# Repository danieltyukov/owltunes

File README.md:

<h1 align="center">OwlTunes</h1>

<p align="center"><b>Your music, one turn away.</b><br>
A Spotify remote with a round AMOLED face and a rotating ring. It charges on your desk and goes
with you in your pocket.</p>

<p align="center"><a href="https://danieltyukov.github.io/owltunes/">Website</a> |
<a href="docs/setup-guide.md">Setup guide</a> |
<a href="docs/design/2026-10-04-owltunes-system-design.md">System design</a> |
<a href="docs/hardware/README.md">Hardware</a></p>

OwlTunes controls the music that is already playing on your phone, laptop or speakers. Turn the
ring to change the volume, tap the cover to pause, press an ear to skip. Drop it on its perch and
it becomes a desk display that charges while it shows what is playing.

Spotify switched off every Car Thing in December 2024. Nobody can do that to OwlTunes: the
firmware, boards and enclosure are open source, it talks to Spotify's Web API directly over Wi-Fi,
and Bluetooth media keys keep working when there is no internet.

| On the desk | In your pocket |
|---|---|
|  |  |

## The device

| | |
|---|---|
| Display | 1.75 inch round AMOLED, 466 x 466, capacitive touch, behind 1.1 mm cover glass |
| Controls | Rotating ring with haptic detents, two ear buttons, a beak button, touch and swipe |
| Brain | ESP32-S3 with 16 MB flash and 8 MB PSRAM |
| Connectivity | Wi-Fi to the Spotify Web API (home network or phone hotspot); Bluetooth LE media keys offline |
| Sensors | Hall sensor for the ring, accelerometer (pick up to wake), ambient light |
| Power | Single-cell LiPo, USB-C, and spring-contact charging on the perch |
| Size | 66 x 84 x 24 mm |
| Perch | Weighted magnetic desk dock that holds the owl at 17.5 degrees |

## How you use it

| Control | Action |
|---|---|
| Ring | Volume on Now Playing; scroll in lists, one haptic tick per item |
| Tap the cover | Play or pause |
| Swipe left or right | Next or previous track |
| Left or right ear | Previous or next track |
| Hold the left ear, turn the ring | Pick one of 8 presets, release to play |
| Hold the right ear | Like the current track |
| Beak | Back; hold for Now Playing |

It also browses your playlists and library, searches, manages the queue and moves playback
between your Spotify Connect devices.

## What it looks like

The screens below come from the desktop simulator, which runs the same UI code as the firmware.

| Now playing | Playlists | Preset wheel | Looking for your phone |
|---|---|---|---|
|  |  |  |  |

## Inside

A 4-layer main board (KiCad 10, assembled by JLCPCB) inside a printed nylon enclosure (build123d,
MJF PA12). The ring carries magnets that a Hall sensor on the board reads, and a small linear
motor gives each detent its click. Every board passes ERC, DRC and a check against the enclosure's
mechanical contract in CI.

The renders on this page are made from the same files: the enclosure and board meshes go into
Blender with `tools/render.sh`, and the screen shows the simulator's output. The album art is a
generated placeholder. The renders were computed on the DelftBlue supercomputer of the Delft High
Performance Computing Centre (DHPC, https://www.tudelft.nl/dhpc), and the owl v0 renders on a TU
Delft EWI compute server.

## Owl v0

| Owl v0 | Inside owl v0 |
|---|---|
|  |  |

The first owl to be built is owl v0: the same face, ring, ears and beak, built round Waveshare's
ESP32-S3-Touch-AMOLED-1.75 kit, which brings the display, the ESP32-S3, USB-C and the battery
charger, so there is no board to order. Six nylon prints hold it, a Hall sensor module reads the
ring's magnets, and tact switches sit under the ears and the beak. It has no perch, haptics or light
sensor yet, and it is 19.7 mm deep. [kit-owl.md](docs/hardware/kit-owl.md) has the parts, wiring
and assembly.

## Status

- **Firmware:** Wi-Fi setup, Spotify linking and playback control run on an ESP32-S3 dev board
  against a real Spotify account, and are tested on the host and in QEMU. Display and touch
  drivers for the rev A board and the Waveshare AMOLED kit build in CI and wait for first light.
- **Owl v0:** the owl built round the Waveshare AMOLED kit, with the ring, ear and beak buttons
  and a 400 mAh cell, ready to order and print ([kit-owl.md](docs/hardware/kit-owl.md)).
- **Hardware rev A:** main board and perch board designed and checked; ordered after owl v0.
- **Enclosure v1:** owl, ring, bezel and perch ready for printing, with the face built around the
  panel's 52.6 mm cover glass.
- **Next:** owl v0 assembled and brought up, the button and ring drivers, then rev A.

Read the [system design](docs/design/2026-10-04-owltunes-system-design.md) for the full picture
and [docs/hardware](docs/hardware/README.md) for the boards.

## Set it up

OwlTunes needs Spotify Premium and your own free Spotify developer app (client ID). It uses the
Authorization Code flow with PKCE, so no client secret is stored on the device or in this
repository. Open the [setup page](https://danieltyukov.github.io/owltunes/setup/) in Chrome or
Edge, connect the owl over USB, add your Wi-Fi networks and client ID, and log in with Spotify.
The [setup guide](docs/setup-guide.md) walks through every step.

## Build it

<details>
<summary>Commands (Linux with CMake 3.22+, Ninja and a C compiler)</summary>

| What | Command |
|---|---|
| Unit tests (with sanitizers) | `tools/test_host.sh` |
| Simulator screenshot tests | `tools/sim.sh` |
| Interactive simulator (needs `libsdl2-dev`) | `cmake -S sim -B build/sim-sdl -G Ninja -DOWL_SIM_SDL=ON && cmake --build build/sim-sdl && build/sim-sdl/owl_sim sdl` |
| Firmware (ESP-IDF v6.1 activated) | `tools/firmware.sh build` |
| Firmware for the Arduino Nano ESP32, and flashing it | `tools/firmware.sh build nano_esp32`, then `tools/firmware.sh flash nano_esp32` |
| Firmware for the owl's rev A board or the Waveshare ESP32-S3-Touch-AMOLED-1.75 kit (display and touch; not yet run on hardware) | `tools/firmware.sh build owltunes_reva` or `tools/firmware.sh build waveshare_amoled_175`, then `flash` with the same board name |
| Hardware tests on the Nano ESP32 (board on USB) | `tools/hil_nano.py --wifi`; with a linked board and your consent, `tools/hil_spotify.py --real-account` |
| Firmware in the QEMU emulator | `tools/qemu_smoke.sh` |
| Setup protocol in QEMU, including a real HTTPS call to Spotify | `tools/qemu_prov_test.py` |
| Setup site: unit and browser tests (Node.js 22) | `cd web && npm ci && npm test && npm run e2e` |
| Setup site: local development server | `cd web && npm run dev` |
| Enclosure tests and exports | see [enclosure/README.md](enclosure/README.md) |
| Hardware checks (KiCad 10) | `tools/hw/check_all.sh` |
| Product renders (Blender 5.2, kicad-cli, uv) | `tools/render.sh` |
| Regenerate the UI fonts (needs Node.js) | `tools/gen_fonts.sh` |

</details>

| Path | Contents |
|---|---|
| `firmware/` | ESP-IDF firmware; shared C code in `firmware/components/`, board support in `firmware/boards/` |
| `sim/` | Desktop simulator and golden screenshots |
| `web/` | The setup site (TypeScript and Vite), published on GitHub Pages |
| `enclosure/` | build123d sources for the owl, owl v0 on the Waveshare kit, the ring and the perch |
| `hardware/` | KiCad 10 projects for the owl main board and the perch board |
| `docs/` | Design documents, hardware notes, setup and protocol guides |
| `tools/` | Build, test, style, render and font scripts |

The UI font is [Inter](https://rsms.me/inter/) (SIL Open Font License, see
`firmware/components/owl_ui/fonts/LICENSE-Inter.txt`).

## Licences

- Software: [MIT](LICENSE)
- Hardware and enclosure designs: [CERN-OHL-P-2.0](LICENSE-HARDWARE)

## Not affiliated with Spotify

OwlTunes is an independent, non-commercial project. It is not affiliated with, endorsed by or
sponsored by Spotify. Spotify is a trademark of Spotify AB.

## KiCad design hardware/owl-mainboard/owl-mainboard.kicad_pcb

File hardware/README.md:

# OwlTunes hardware

KiCad 10 projects for the owl main board (`owl-mainboard/`, 4 layers) and the perch board with its
snap-off owl dock-pad section (`perch-dock/`, 2 layers). Shared symbols and footprints are in
`lib/`. Licence: CERN-OHL-P-2.0 (`LICENSE-HARDWARE`).

Documentation: docs/hardware/README.md.

Each board has a `design.toml` that lists every part, its LCSC number and its pin-to-net map. The
schematic must match it exactly:

| Command | Checks |
|---|---|
| `tools/hw/check_all.sh` | Everything below, as CI runs it |
| `python3 tools/hw/hw_titleblock.py --check owl-mainboard` | Title blocks (title, Rev A, company, licence, date) of every schematic and the PCB; without `--check` it writes them |
| `python3 tools/hw/hw_netlist.py owl-mainboard` | Connectivity against `design.toml` |
| `python3 tools/hw/hw_bom.py owl-mainboard` | `LCSC Part #` and `MPN` fields |
| `python3 tools/hw/hw_kicad.py` | ERC (and DRC once enabled in `boards.toml`), reports in `build/hardware/` |
| `python3 tools/hw/hw_contract.py check owl-mainboard` | Outline and fixed parts against the enclosure contract |
| `python3 tools/hw/hw_stock.py owl-mainboard --boards 5` | JLCPCB stock (needs network) |

`tools/hw/hw_setup.py <board>` applies `setup.toml` (stackup, origins, JLCPCB rules, net classes).
The stackup in `setup.toml` is written into each PCB by `hw_setup.py`. Main board: JLCPCB 4-layer
1.0 mm, modelled on JLC04101H-7628 (35 um outer copper, 7628 prepreg 0.2104 mm, 15.2 um inner
copper); the core thickness (0.4788 mm) is chosen so the stack adds up to 1.0 mm and is to be
confirmed against https://jlcpcb.com/impedance on the order day. Perch board: 2-layer 1.6 mm FR-4.
A test checks that each stack adds up to the board thickness.

`hw_stock.py` writes prices only below the main checkout's `private/` folder.

Coordinates: the display centre is at (100, 100) on the board page, with X right and Y down.
Fabrication outputs (`production/`) are generated, not tracked; releases carry them.

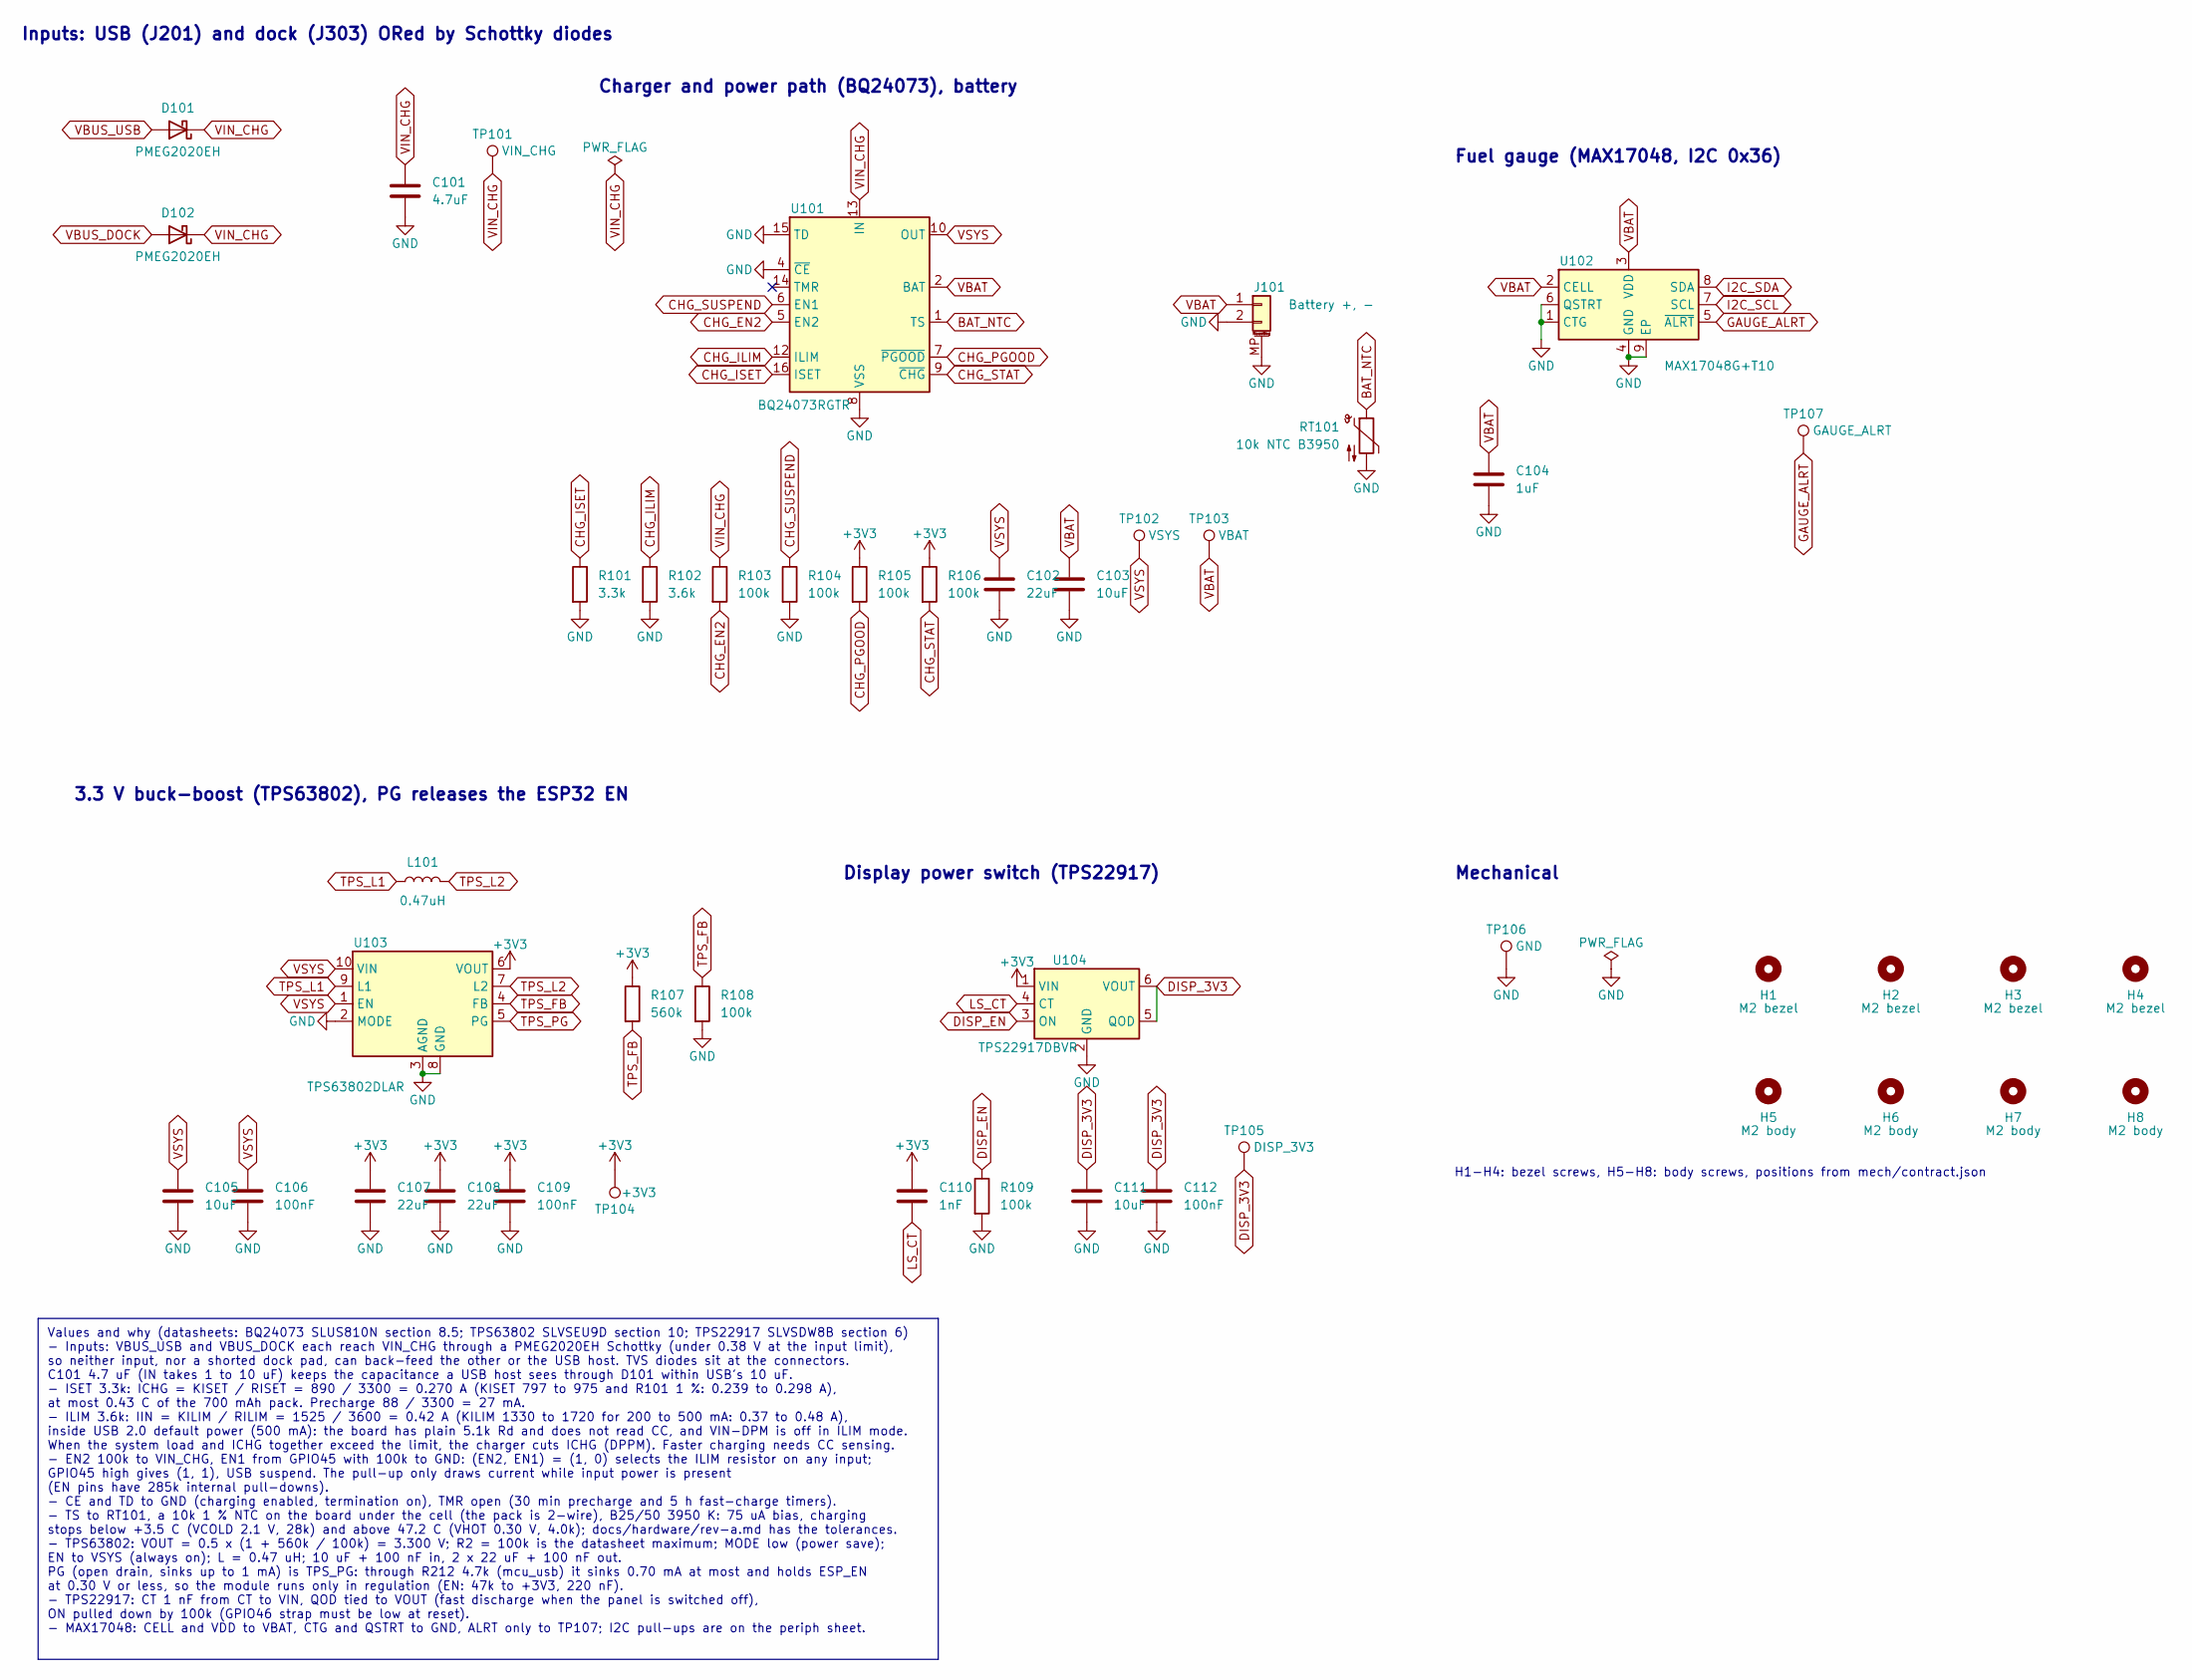
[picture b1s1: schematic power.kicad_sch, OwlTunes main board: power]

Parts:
C101: 4.7uF; C_0603_1608Metric; MPN CL10A475KO8NNNC; LCSC Part # C19666
C102, C107, C108: 22uF; C_0603_1608Metric; MPN CL10A226MQ8NRNC; LCSC Part # C59461
C103, C105, C111: 10uF; C_0603_1608Metric; MPN CL10A106KP8NNNC; LCSC Part # C19702
C104: 1uF; C_0402_1005Metric; MPN CL05A105KA5NQNC; LCSC Part # C52923
C106, C109, C112: 100nF; C_0402_1005Metric; MPN CL05B104KO5NNNC; LCSC Part # C1525
C110: 1nF; C_0402_1005Metric; MPN 0402B102K500NT; LCSC Part # C1523
D101, D102: PMEG2020EH; D_SOD-123F; MPN PMEG2020EH,115; LCSC Part # C456104
H1, H2, H3, H4: M2 bezel; MountingHole_2.2mm_M2
H5, H6, H7, H8: M2 body; MountingHole_2.2mm_M2
J101: Battery +, -; JST_PH_S2B-PH-SM4-TB_1x02-1MP_P2.00mm_Horizontal; MPN S2B-PH-SM4-TB(LF)(SN); LCSC Part # C295747
L101: 0.47uH; L_Murata_DFE201612E; MPN DFE201612E-R47M=P2; LCSC Part # C668312
R101: 3.3k; R_0402_1005Metric; MPN 0402WGF3301TCE; LCSC Part # C25890
R102: 3.6k; R_0402_1005Metric; MPN 0402WGF3601TCE; LCSC Part # C25891
R103, R104, R105, R106, R108, R109: 100k; R_0402_1005Metric; MPN 0402WGF1003TCE; LCSC Part # C25741
R107: 560k; R_0402_1005Metric; MPN 0402WGF5603TCE; LCSC Part # C132339
RT101: 10k NTC B3950; R_0402_1005Metric; MPN SDNT1005X103F3950FTF; LCSC Part # C95939
TP101: VIN_CHG; TestPoint_Pad_D1.0mm
TP102: VSYS; TestPoint_Pad_D1.0mm
TP103: VBAT; TestPoint_Pad_D1.0mm
TP104: +3V3; TestPoint_Pad_D1.0mm
TP105: DISP_3V3; TestPoint_Pad_D1.0mm
TP106: GND; TestPoint_Pad_D1.0mm
TP107: GAUGE_ALRT; TestPoint_Pad_D1.0mm
U101: BQ24073RGTR; VQFN-16-1EP_3x3mm_P0.5mm_EP1.6x1.6mm_ThermalVias_Drill0.3; MPN BQ24073RGTR; LCSC Part # C15220
U102: MAX17048G+T10; Maxim_TDFN-8-1EP_2x2mm_P0.5mm; MPN MAX17048G+T10; LCSC Part # C2682616
U103: TPS63802DLAR; TI_DLA_VSON-10_2x3mm_P0.5mm; MPN TPS63802DLAR; LCSC Part # C2845237
U104: TPS22917DBVR; SOT-23-6; MPN TPS22917DBVR; LCSC Part # C2681320

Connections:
+3V3: C107.1, C108.1, C109.1, C110.1, R105.1, R106.1, R107.1, TP104.1, U103.6 (VOUT), U104.1 (VIN); also elsewhere on the board
BAT_NTC: RT101.1, U101.1 (TS)
CHG_EN2: R103.2, U101.5 (EN2)
CHG_ILIM: R102.1, U101.12 (ILIM)
CHG_ISET: R101.1, U101.16 (ISET)
CHG_PGOOD: R105.2, U101.7 (~PGOOD); also elsewhere on the board
CHG_STAT: R106.2, U101.9 (~CHG); also elsewhere on the board
CHG_SUSPEND: R104.1, U101.6 (EN1); also elsewhere on the board
DISP_3V3: C111.1, C112.1, TP105.1, U104.5 (QOD), U104.6 (VOUT); also elsewhere on the board
DISP_EN: R109.1, U104.3 (ON); also elsewhere on the board
GAUGE_ALRT: TP107.1, U102.5 (~ALRT)
GND: C101.2, C102.2, C103.2, C104.2, C105.2, C106.2, C107.2, C108.2, C109.2, C111.2, C112.2, J101.2, J101.MP (MountPin), R101.2, R102.2, R104.2, R108.2, R109.2, RT101.2, TP106.1, U101.4 (~CE), U101.8 (VSS), U101.15 (TD), U101.17 (VSS), U102.1 (CTG), U102.4 (GND), U102.6 (QSTRT), U102.9 (EP), U103.2 (MODE), U103.3 (AGND), U103.8 (GND), U104.2 (GND); also elsewhere on the board
I2C_SCL: U102.7 (SCL); also elsewhere on the board
I2C_SDA: U102.8 (SDA); also elsewhere on the board
LS_CT: C110.2, U104.4 (CT)
TPS_FB: R107.2, R108.1, U103.4 (FB)
TPS_L1: L101.1, U103.9 (L1)
TPS_L2: L101.2, U103.7 (L2)
TPS_PG: U103.5 (PG); also elsewhere on the board
VBAT: C103.1, C104.1, J101.1, TP103.1, U101.2 (BAT), U101.3 (BAT), U102.2 (CELL), U102.3 (VDD)
VBUS_DOCK: D102.2 (A); also elsewhere on the board
VBUS_USB: D101.2 (A); also elsewhere on the board
VIN_CHG: C101.1, D101.1 (K), D102.1 (K), R103.1, TP101.1, U101.13 (IN)
VSYS: C102.1, C105.1, C106.1, TP102.1, U101.10 (OUT), U101.11 (OUT), U103.1 (EN), U103.10 (VIN)

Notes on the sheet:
Charger and power path (BQ24073), battery
3.3 V buck-boost (TPS63802), PG releases the ESP32 EN
Fuel gauge (MAX17048, I2C 0x36)
Display power switch (TPS22917)
Mechanical
H1-H4: bezel screws, H5-H8: body screws, positions from mech/contract.json
Inputs: USB (J201) and dock (J303) ORed by Schottky diodes
Values and why (datasheets: BQ24073 SLUS810N section 8.5; TPS63802 SLVSEU9D section 10; TPS22917 SLVSDW8B section 6) - Inputs: VBUS_USB and VBUS_DOCK each reach VIN_CHG through a PMEG2020EH Schottky (under 0.38 V at the input limit), so neither input, nor a shorted dock pad, can back-feed the other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

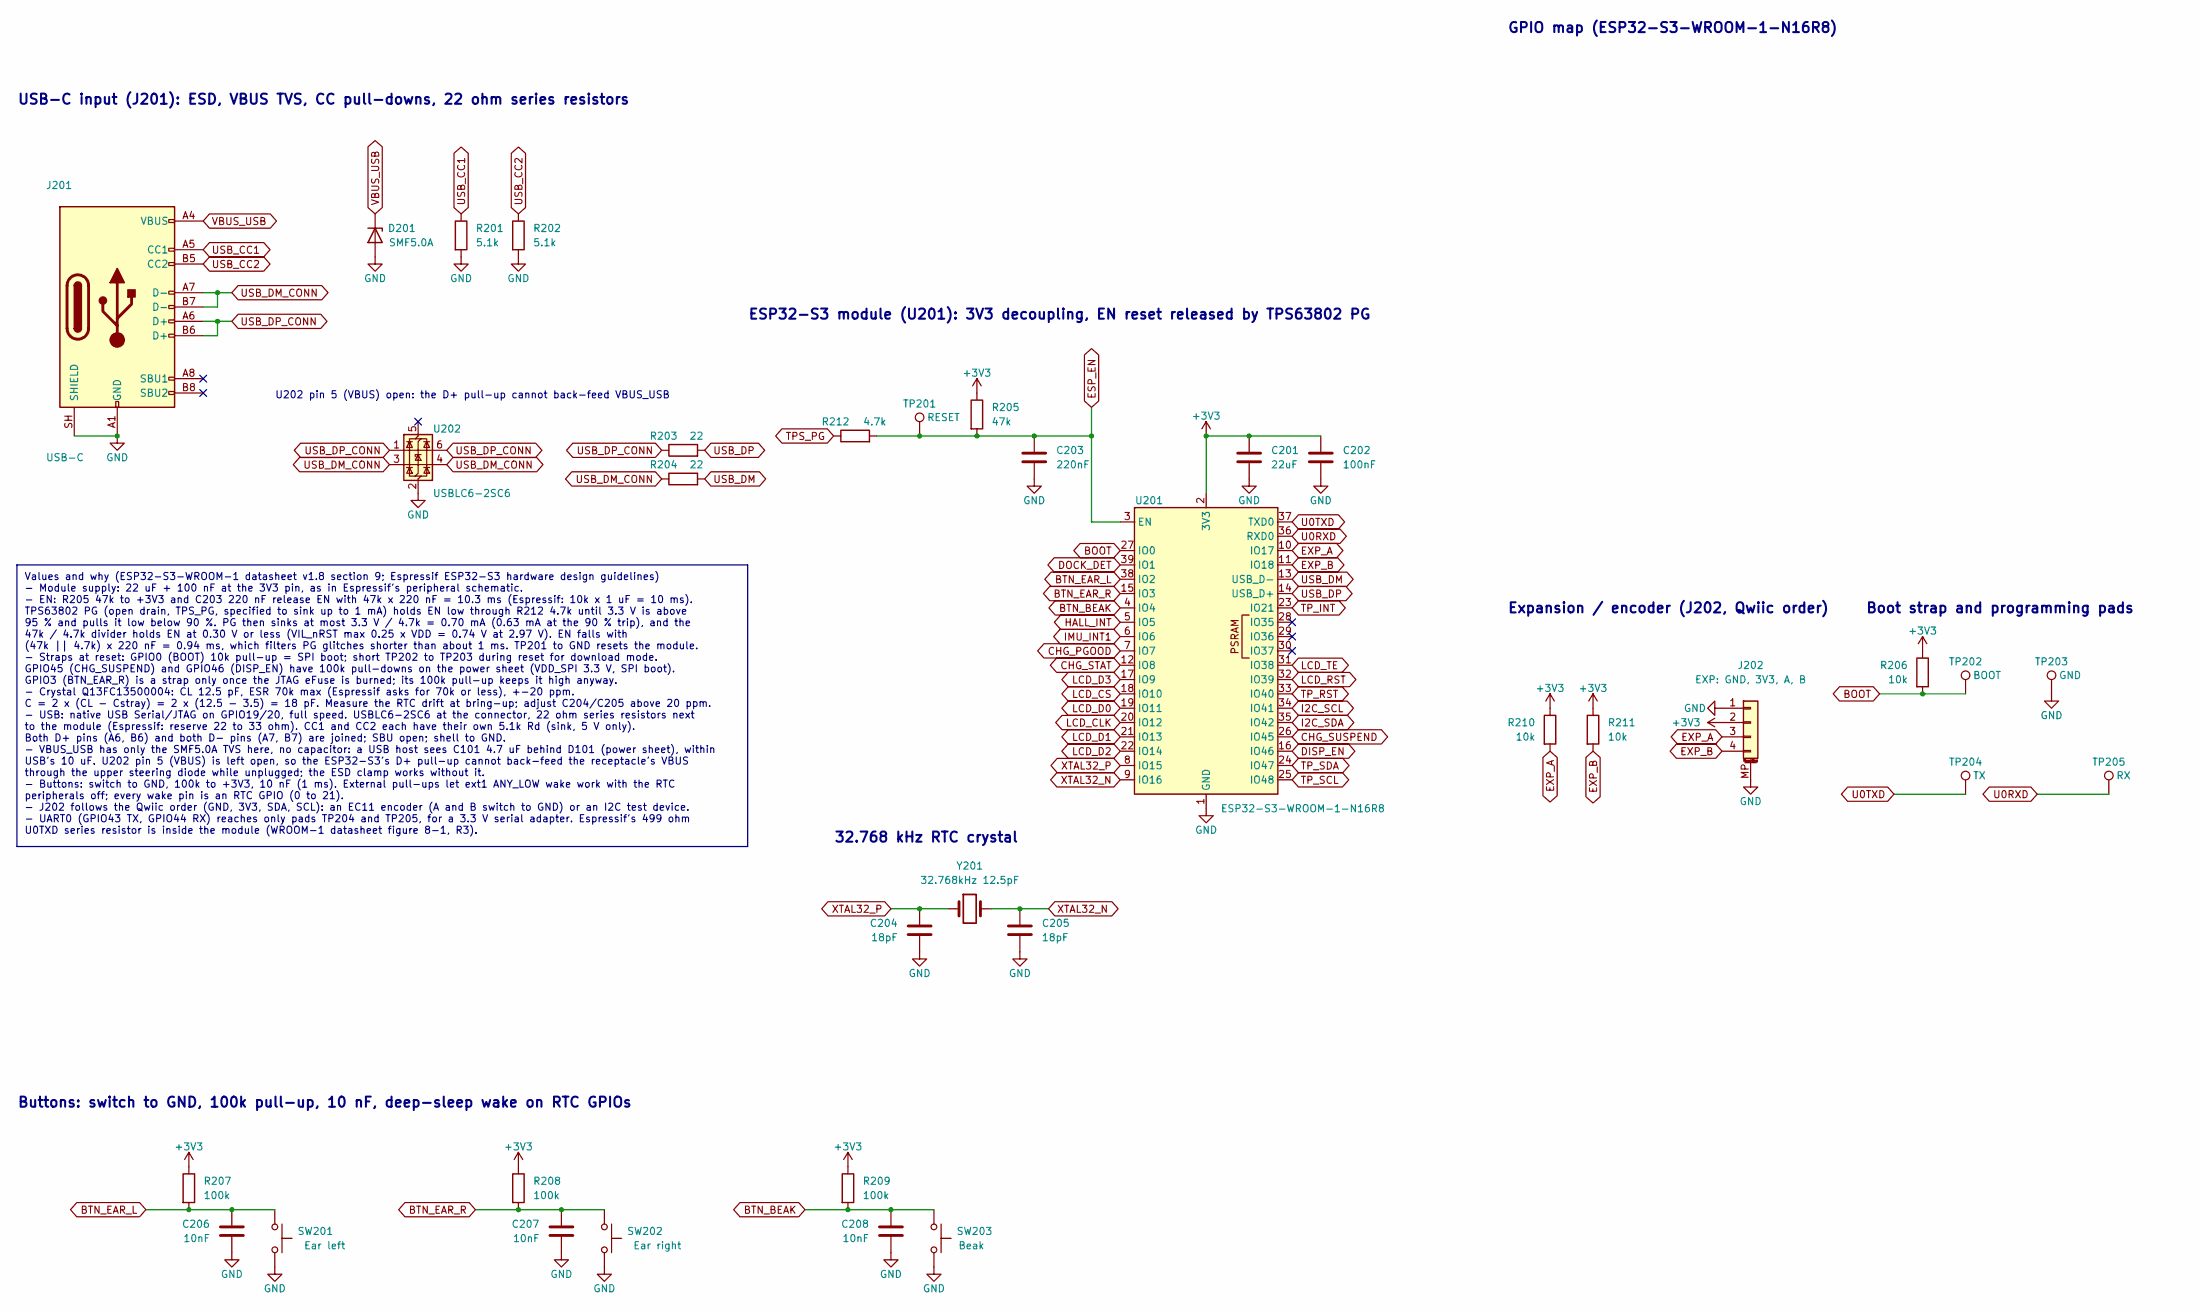
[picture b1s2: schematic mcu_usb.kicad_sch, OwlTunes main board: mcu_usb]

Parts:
C201: 22uF; C_0603_1608Metric; MPN CL10A226MQ8NRNC; LCSC Part # C59461
C202: 100nF; C_0402_1005Metric; MPN CL05B104KO5NNNC; LCSC Part # C1525
C203: 220nF; C_0402_1005Metric; MPN CL05B224KO5NNNC; LCSC Part # C16772
C204, C205: 18pF; C_0402_1005Metric; MPN 0402CG180J500NT; LCSC Part # C1549
C206, C207, C208: 10nF; C_0402_1005Metric; MPN CL05B103KB5NNNC; LCSC Part # C15195
D201: SMF5.0A; D_SOD-123F; MPN SMF5.0A; LCSC Part # C193402
J201: USB-C; USB_C_Receptacle_HRO_TYPE-C-31-M-12; MPN TYPE-C-31-M-12; LCSC Part # C165948
J202: EXP: GND, 3V3, A, B; JST_SH_SM04B-SRSS-TB_1x04-1MP_P1.00mm_Horizontal; MPN SM04B-SRSS-TB(LF)(SN); LCSC Part # C160404
R201, R202: 5.1k; R_0402_1005Metric; MPN 0402WGF5101TCE; LCSC Part # C25905
R203, R204: 22; R_0402_1005Metric; MPN 0402WGF220JTCE; LCSC Part # C25092
R205: 47k; R_0402_1005Metric; MPN 0402WGF4702TCE; LCSC Part # C25792
R206, R210, R211: 10k; R_0402_1005Metric; MPN 0402WGF1002TCE; LCSC Part # C25744
R207, R208, R209: 100k; R_0402_1005Metric; MPN 0402WGF1003TCE; LCSC Part # C25741
R212: 4.7k; R_0402_1005Metric; MPN 0402WGF4701TCE; LCSC Part # C25900
SW201: Ear left; SW_SPST_EVQP7A; MPN EVQP7A01P; LCSC Part # C79167
SW202: Ear right; SW_SPST_EVQP7A; MPN EVQP7A01P; LCSC Part # C79167
SW203: Beak; SW_SPST_TS-1088-xR020; MPN TS-1088-AR02016; LCSC Part # C720477
TP201: RESET; TestPoint_Pad_D1.5mm
TP202: BOOT; TestPoint_Pad_D1.5mm
TP203: GND; TestPoint_Pad_D1.5mm
TP204: TX; TestPoint_Pad_D1.0mm
TP205: RX; TestPoint_Pad_D1.0mm
U201: ESP32-S3-WROOM-1-N16R8; ESP32-S3-WROOM-1_Drill0.3; MPN ESP32-S3-WROOM-1-N16R8; LCSC Part # C2913202
U202: USBLC6-2SC6; SOT-23-6; MPN USBLC6-2SC6; LCSC Part # C7519
Y201: 32.768kHz 12.5pF; Crystal_SMD_3215-2Pin_3.2x1.5mm; MPN Q13FC13500004; LCSC Part # C32346

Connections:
+3V3: C201.1, C202.1, J202.2, R205.1, R206.1, R207.1, R208.1, R209.1, R210.1, R211.1, U201.2 (3V3); also elsewhere on the board
BOOT: R206.2, TP202.1, U201.27 (IO0)
BTN_BEAK: C208.1, R209.2, SW203.1, U201.4 (IO4)
BTN_EAR_L: C206.1, R207.2, SW201.1, U201.38 (IO2)
BTN_EAR_R: C207.1, R208.2, SW202.1, U201.15 (IO3)
CHG_PGOOD: U201.7 (IO7); also elsewhere on the board
CHG_STAT: U201.12 (IO8); also elsewhere on the board
CHG_SUSPEND: U201.26 (IO45); also elsewhere on the board
DISP_EN: U201.16 (IO46); also elsewhere on the board
DOCK_DET: U201.39 (IO1); also elsewhere on the board
ESP_EN: C203.1, R205.2, R212.2, TP201.1, U201.3 (EN)
EXP_A: J202.3, R210.2, U201.10 (IO17)
EXP_B: J202.4, R211.2, U201.11 (IO18)
GND: C201.2, C202.2, C203.2, C204.2, C205.2, C206.2, C207.2, C208.2, D201.2 (A), J201.A1 (GND), J201.A12 (GND), J201.B1 (GND), J201.B12 (GND), J201.SH (SHIELD), J202.1, J202.MP (MountPin), R201.2, R202.2, SW201.2, SW202.2, SW203.2, TP203.1, U201.1 (GND), U201.40 (GND), U201.41 (GND), U202.2 (GND); also elsewhere on the board
HALL_INT: U201.5 (IO5); also elsewhere on the board
I2C_SCL: U201.34 (IO41); also elsewhere on the board
I2C_SDA: U201.35 (IO42); also elsewhere on the board
IMU_INT1: U201.6 (IO6); also elsewhere on the board
LCD_CLK: U201.20 (IO12); also elsewhere on the board
LCD_CS: U201.18 (IO10); also elsewhere on the board
LCD_D0: U201.19 (IO11); also elsewhere on the board
LCD_D1: U201.21 (IO13); also elsewhere on the board
LCD_D2: U201.22 (IO14); also elsewhere on the board
LCD_D3: U201.17 (IO9); also elsewhere on the board
LCD_RST: U201.32 (IO39); also elsewhere on the board
LCD_TE: U201.31 (IO38); also elsewhere on the board
TPS_PG: R212.1; also elsewhere on the board
TP_INT: U201.23 (IO21); also elsewhere on the board
TP_RST: U201.33 (IO40); also elsewhere on the board
TP_SCL: U201.25 (IO48); also elsewhere on the board
TP_SDA: U201.24 (IO47); also elsewhere on the board
U0RXD: TP205.1, U201.36 (RXD0)
U0TXD: TP204.1, U201.37 (TXD0)
USB_CC1: J201.A5 (CC1), R201.1
USB_CC2: J201.B5 (CC2), R202.1
USB_DM: R204.2, U201.13 (USB_D-)
USB_DM_CONN: J201.A7 (D-), J201.B7 (D-), R204.1, U202.3 (I/O2), U202.4 (I/O2)
USB_DP: R203.2, U201.14 (USB_D+)
USB_DP_CONN: J201.A6 (D+), J201.B6 (D+), R203.1, U202.1 (I/O1), U202.6 (I/O1)
VBUS_USB: D201.1 (K), J201.A4 (VBUS), J201.A9 (VBUS), J201.B4 (VBUS), J201.B9 (VBUS); also elsewhere on the board
XTAL32_N: C205.1, U201.9 (IO16), Y201.2
XTAL32_P: C204.1, U201.8 (IO15), Y201.1

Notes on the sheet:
GPIO map (ESP32-S3-WROOM-1-N16R8)
USB-C input (J201): ESD, VBUS TVS, CC pull-downs, 22 ohm series resistors
ESP32-S3 module (U201): 3V3 decoupling, EN reset released by TPS63802 PG
Boot strap and programming pads
Buttons: switch to GND, 100k pull-up, 10 nF, deep-sleep wake on RTC GPIOs
U202 pin 5 (VBUS) open: the D+ pull-up cannot back-feed VBUS_USB
Expansion / encoder (J202, Qwiic order)
32.768 kHz RTC crystal
Values and why (ESP32-S3-WROOM-1 datasheet v1.8 section 9; Espressif ESP32-S3 hardware design guidelines) - Module supply: 22 uF + 100 nF at the 3V3 pin, as in Espressif's peripheral schematic. - EN: R205 47k to +3V3 and C203 220 nF release EN with 47k x 220 nF = 10.3 ms (Espressif: 10k x 1 uF = 10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

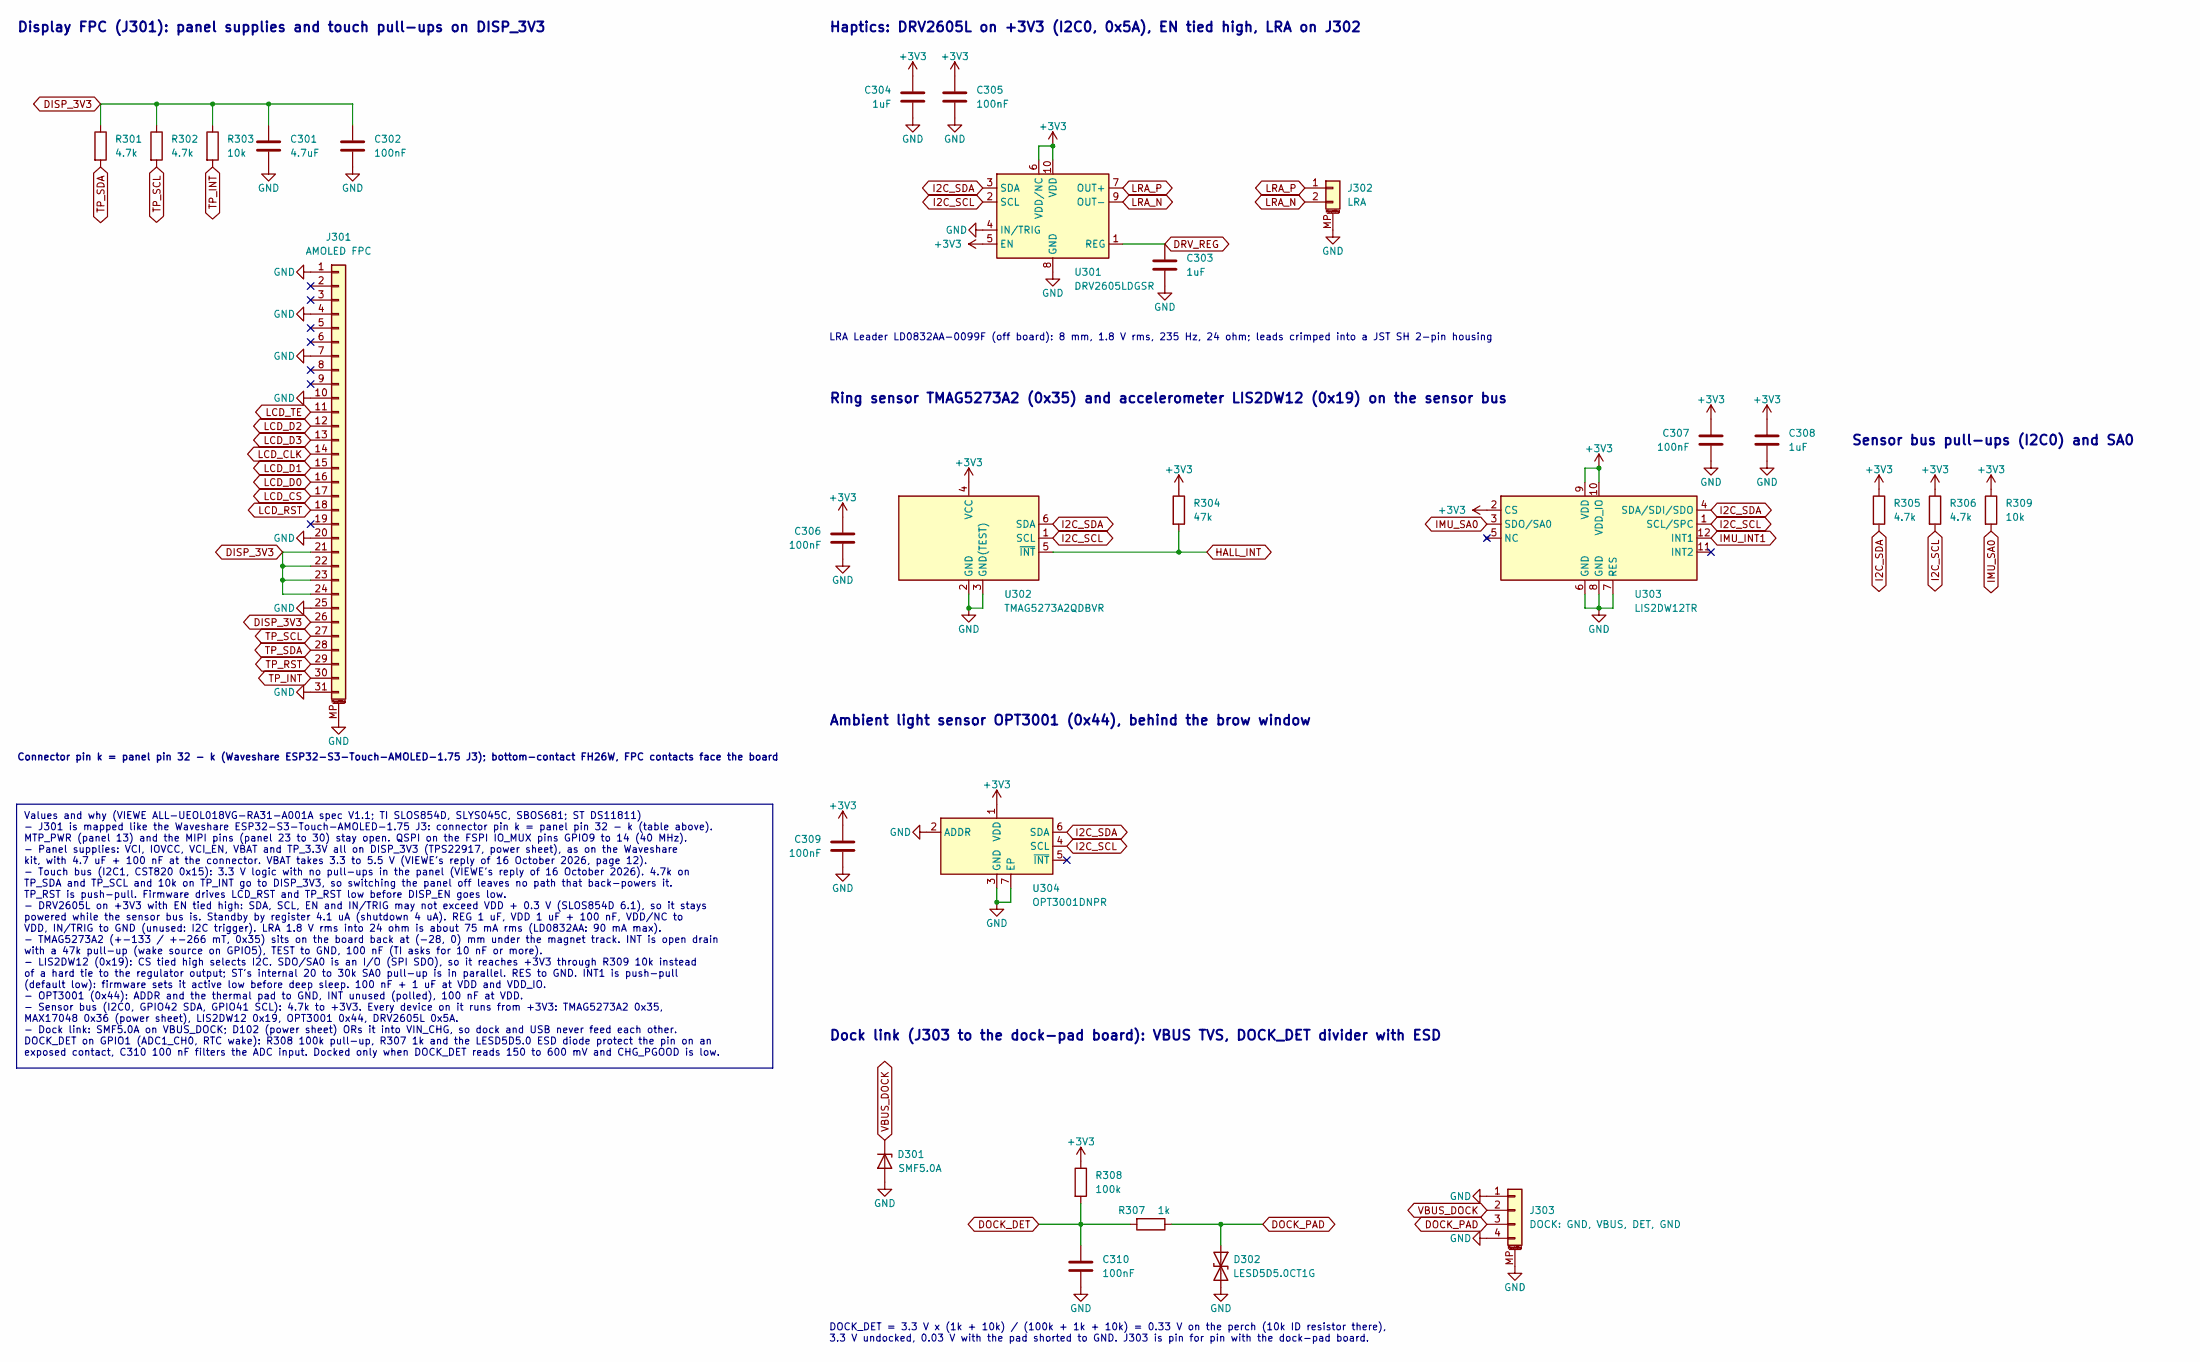
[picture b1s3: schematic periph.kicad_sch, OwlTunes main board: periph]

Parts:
C301: 4.7uF; C_0402_1005Metric; MPN CL05A475MP5NRNC; LCSC Part # C23733
C302, C305, C306, C307, C309, C310: 100nF; C_0402_1005Metric; MPN CL05B104KO5NNNC; LCSC Part # C1525
C303, C304, C308: 1uF; C_0402_1005Metric; MPN CL05A105KA5NQNC; LCSC Part # C52923
D301: SMF5.0A; D_SOD-123F; MPN SMF5.0A; LCSC Part # C193402
D302: LESD5D5.0CT1G; D_SOD-523; MPN LESD5D5.0CT1G; LCSC Part # C5274290
J301: AMOLED FPC; Hirose_FH26W-31S-0.3SHW_1x31-1MP_P0.30mm_Horizontal; MPN FH26W-31S-0.3SHW(60); LCSC Part # C2973806
J302: LRA; JST_SH_SM02B-SRSS-TB_1x02-1MP_P1.00mm_Horizontal; MPN SM02B-SRSS-TB(LF)(SN); LCSC Part # C160402
J303: DOCK: GND, VBUS, DET, GND; JST_SH_SM04B-SRSS-TB_1x04-1MP_P1.00mm_Horizontal; MPN SM04B-SRSS-TB(LF)(SN); LCSC Part # C160404
R301, R302, R305, R306: 4.7k; R_0402_1005Metric; MPN 0402WGF4701TCE; LCSC Part # C25900
R303, R309: 10k; R_0402_1005Metric; MPN 0402WGF1002TCE; LCSC Part # C25744
R304: 47k; R_0402_1005Metric; MPN 0402WGF4702TCE; LCSC Part # C25792
R307: 1k; R_0402_1005Metric; MPN 0402WGF1001TCE; LCSC Part # C11702
R308: 100k; R_0402_1005Metric; MPN 0402WGF1003TCE; LCSC Part # C25741
U301: DRV2605LDGSR; TSSOP-10_3x3mm_P0.5mm; MPN DRV2605LDGSR; LCSC Part # C527464
U302: TMAG5273A2QDBVR; SOT-23-6; MPN TMAG5273A2QDBVR; LCSC Part # C3715882
U303: LIS2DW12TR; LGA-12_2x2mm_P0.5mm; MPN LIS2DW12TR; LCSC Part # C189624
U304: OPT3001DNPR; TI_DNP_USON-6-1EP_2x2mm_P0.65mm; MPN OPT3001DNPR; LCSC Part # C90462

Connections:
+3V3: C304.1, C305.1, C306.1, C307.1, C308.1, C309.1, R304.1, R305.1, R306.1, R308.1, R309.1, U301.5 (EN), U301.6 (VDD/NC), U301.10 (VDD), U302.4 (VCC), U303.2 (CS), U303.9 (VDD), U303.10 (VDD_IO), U304.1 (VDD); also elsewhere on the board
DISP_3V3: C301.1, C302.1, J301.21, J301.22, J301.23, J301.24, J301.26, R301.1, R302.1, R303.1; also elsewhere on the board
DOCK_DET: C310.1, R307.2, R308.2; also elsewhere on the board
DOCK_PAD: D302.1 (A1), J303.3, R307.1
DRV_REG: C303.1, U301.1 (REG)
GND: C301.2, C302.2, C303.2, C304.2, C305.2, C306.2, C307.2, C308.2, C309.2, C310.2, D301.2 (A), D302.2 (A2), J301.1, J301.4, J301.7, J301.10, J301.20, J301.25, J301.31, J301.MP (MountPin), J302.MP (MountPin), J303.1, J303.4, J303.MP (MountPin), U301.4 (IN/TRIG), U301.8 (GND), U302.2 (GND), U302.3 (GND(TEST)), U303.6 (GND), U303.7 (RES), U303.8 (GND), U304.2 (ADDR), U304.3 (GND), U304.7 (EP); also elsewhere on the board
HALL_INT: R304.2, U302.5 (~INT); also elsewhere on the board
I2C_SCL: R306.2, U301.2 (SCL), U302.1 (SCL), U303.1 (SCL/SPC), U304.4 (SCL); also elsewhere on the board
I2C_SDA: R305.2, U301.3 (SDA), U302.6 (SDA), U303.4 (SDA/SDI/SDO), U304.6 (SDA); also elsewhere on the board
IMU_INT1: U303.12 (INT1); also elsewhere on the board
IMU_SA0: R309.2, U303.3 (SDO/SA0)
LCD_CLK: J301.14; also elsewhere on the board
LCD_CS: J301.17; also elsewhere on the board
LCD_D0: J301.16; also elsewhere on the board
LCD_D1: J301.15; also elsewhere on the board
LCD_D2: J301.12; also elsewhere on the board
LCD_D3: J301.13; also elsewhere on the board
LCD_RST: J301.18; also elsewhere on the board
LCD_TE: J301.11; also elsewhere on the board
LRA_N: J302.2, U301.9 (OUT-)
LRA_P: J302.1, U301.7 (OUT+)
TP_INT: J301.30, R303.2; also elsewhere on the board
TP_RST: J301.29; also elsewhere on the board
TP_SCL: J301.27, R302.2; also elsewhere on the board
TP_SDA: J301.28, R301.2; also elsewhere on the board
VBUS_DOCK: D301.1 (K), J303.2; also elsewhere on the board

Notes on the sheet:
LRA Leader LD0832AA-0099F (off board): 8 mm, 1.8 V rms, 235 Hz, 24 ohm; leads crimped into a JST SH 2-pin housing
Sensor bus pull-ups (I2C0) and SA0
Ambient light sensor OPT3001 (0x44), behind the brow window
Dock link (J303 to the dock-pad board): VBUS TVS, DOCK_DET divider with ESD
Haptics: DRV2605L on +3V3 (I2C0, 0x5A), EN tied high, LRA on J302
Display FPC (J301): panel supplies and touch pull-ups on DISP_3V3
Connector pin k = panel pin 32 - k (Waveshare ESP32-S3-Touch-AMOLED-1.75 J3); bottom-contact FH26W, FPC contacts face the board
Ring sensor TMAG5273A2 (0x35) and accelerometer LIS2DW12 (0x19) on the sensor bus
DOCK_DET = 3.3 V x (1k + 10k) / (100k + 1k + 10k) = 0.33 V on the perch (10k ID resistor there), 3.3 V undocked, 0.03 V with the pad shorted to GND. J303 is pin for pin with the dock-pad board.
Values and why (VIEWE ALL-UEOL018VG-RA31-A001A spec V1.1; TI SLOS854D, SLYS045C, SBOS681; ST DS11811) - J301 is mapped like the Waveshare ESP32-S3-Touch-AMOLED-1.75 J3: connector pin k = panel pin 32 - k (table above). MTP_PWR (panel 13) and the MIPI pins (panel 23 to 30) stay open. QSPI on the FSP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

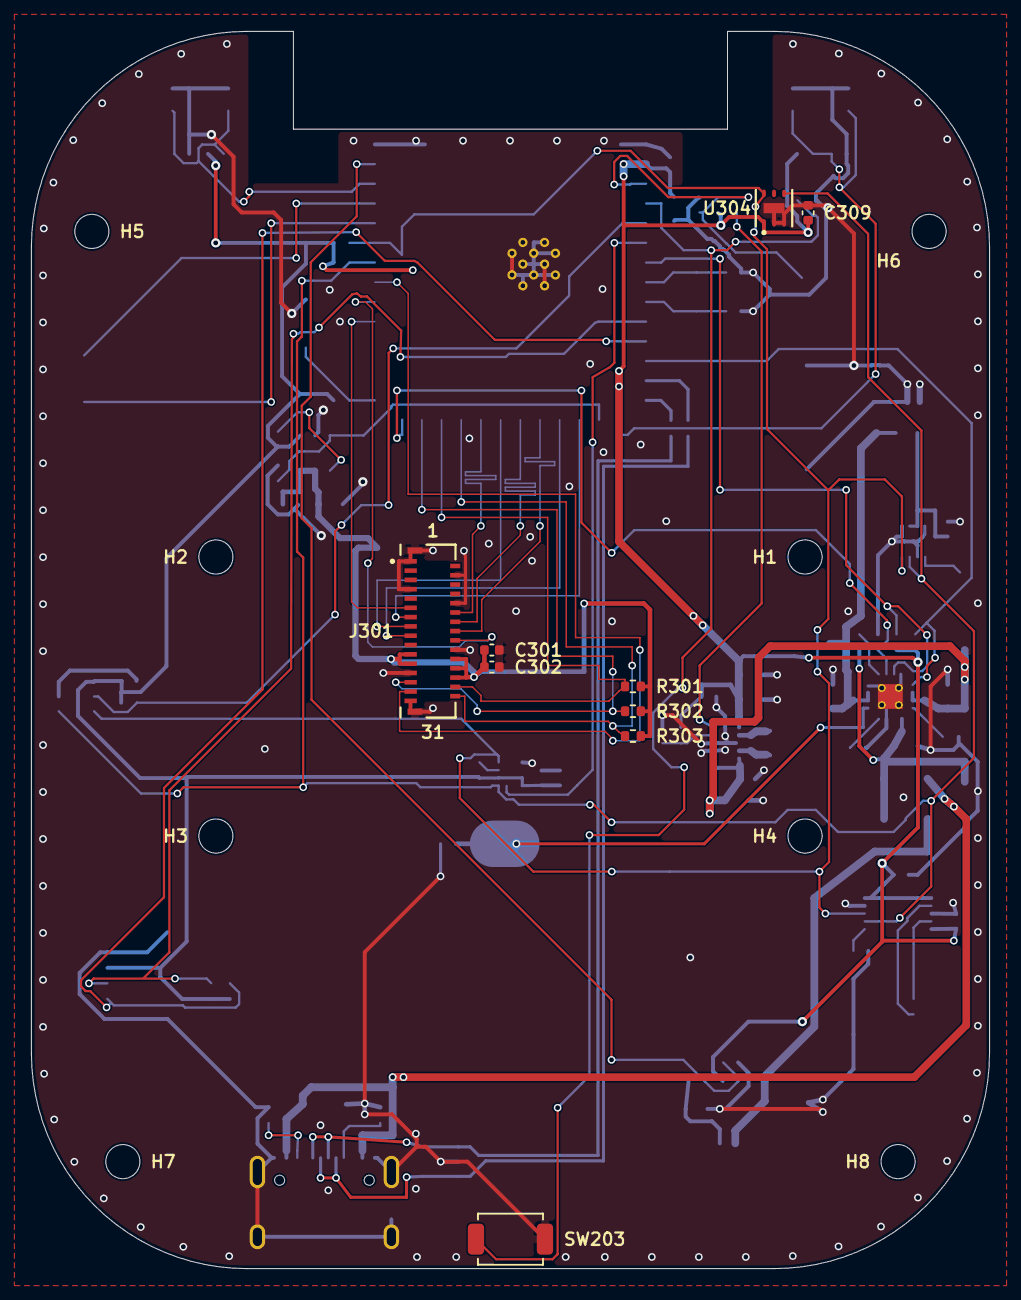
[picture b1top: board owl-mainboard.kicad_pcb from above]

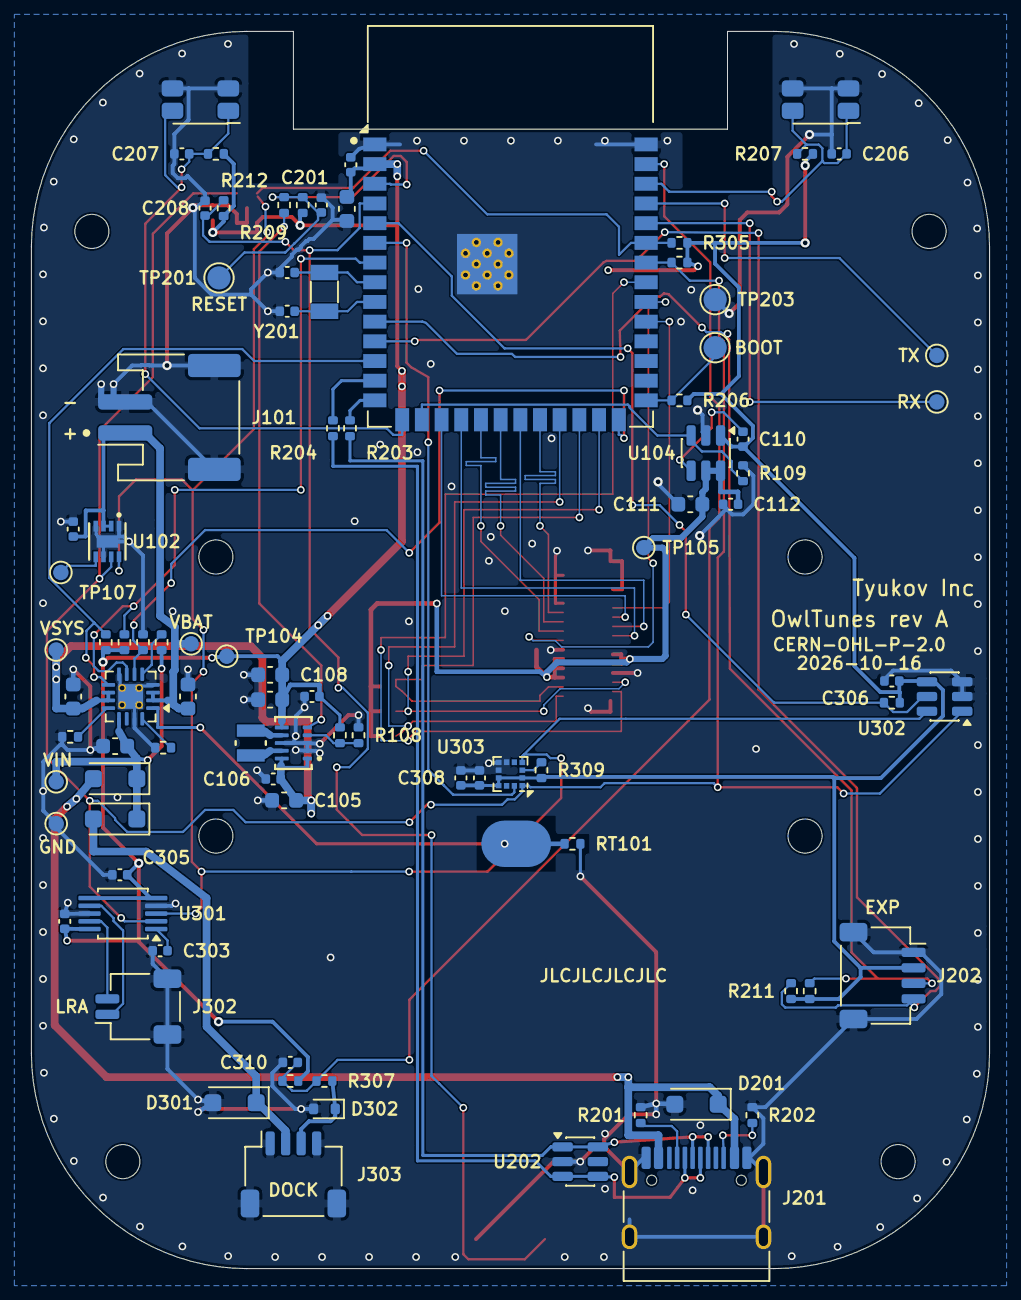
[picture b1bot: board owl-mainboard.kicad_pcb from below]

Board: 4 copper layers, 61.8 x 79.8 mm, 107 parts (90 on the bottom side), 61 nets.
